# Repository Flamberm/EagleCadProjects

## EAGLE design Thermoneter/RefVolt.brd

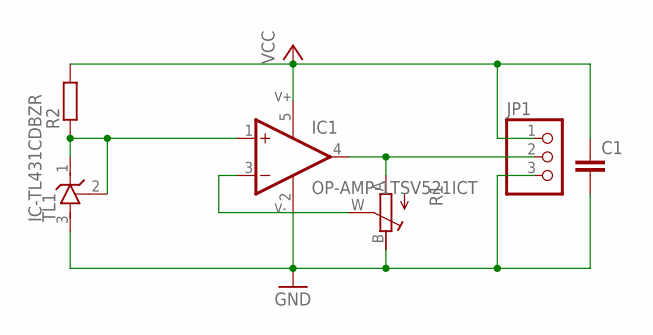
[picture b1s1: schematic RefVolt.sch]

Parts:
C1: CAP_0805; C0805
IC1: OP-AMP-1TSV521ICT; SC70-5L
JP1: PINHD-1X3/90; 1X03/90
R1: R_POTTURN-X; RJ9W
R2: R_0805; R0805
TL1: IC-TL431CDBZR; SOT23

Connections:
GND: C1.2, IC1.2 (V-), JP1.3, R1.B (E), TL1.3 (A)
unnamed: IC1.3 (-IN), R1.W (S)
unnamed: IC1.4 (OUT), JP1.2, R1.A
unnamed: IC1.1 (+IN), R2.1, TL1.1 (C), TL1.2 (R)
VCC: C1.1, IC1.5 (V+), JP1.1, R2.2

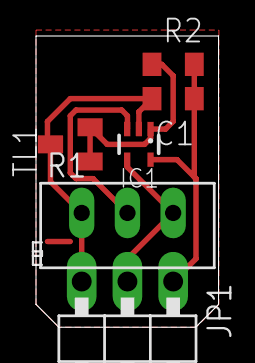
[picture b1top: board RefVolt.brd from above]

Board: 2 copper layers, 10.1 x 16.2 mm, 6 parts (0 on the bottom side), 5 nets.

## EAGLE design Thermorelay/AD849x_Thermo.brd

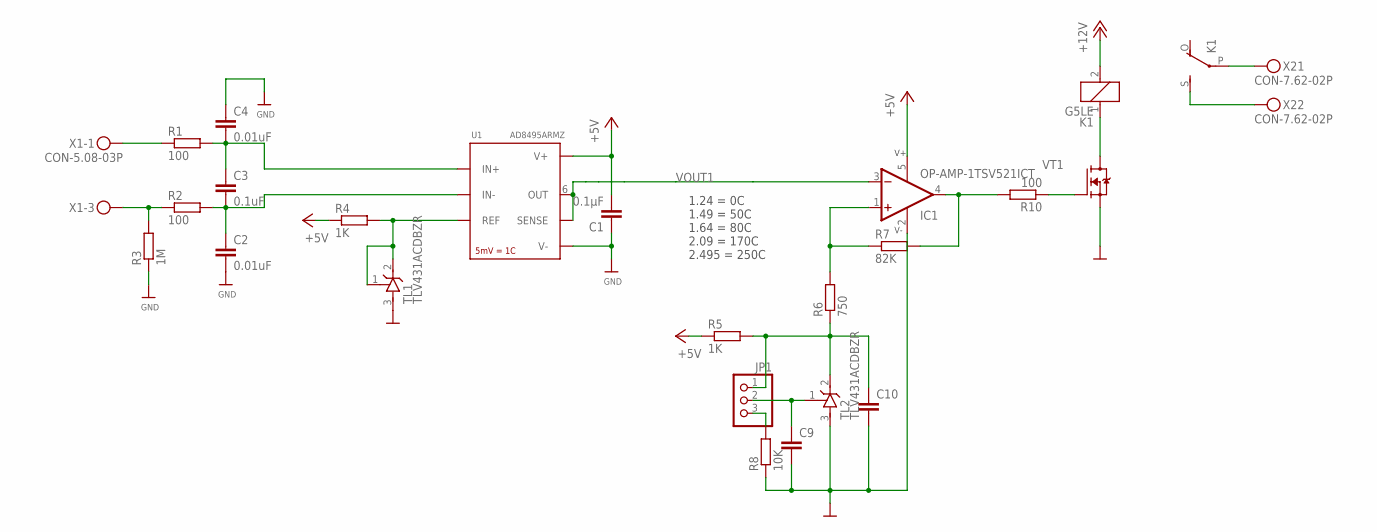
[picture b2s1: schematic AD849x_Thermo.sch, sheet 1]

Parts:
C1: 0.1µF; CAP0805
C2, C4: 0.01uF; CAP0805
C3: 0.1uF; CAP0805
C9, C10: CAP_1206; CAP1206
IC1: OP-AMP-1TSV521ICT; SC70-5L
JP1: PINHD-1X3; 1X03
K1: G5LE
R1, R2, R10: 100; RESC2012X50
R3: 1M; RESC2012X50
R4, R5: 1K; RESC2012X50
R6: 750; RESC2012X50
R7: 82K; RESC2012X50
R8: 10K; RESC2012X50
TL1, TL2: TLV431ACDBZR; SOT95P240X115-3
U1: AD8495ARMZ; MSOP-8
VT1: FET-NSOT-23; SOT95P240X115-3
X1: CON-5.08-03P; MKDSN1,5/3-5,08
X2: CON-7.62-02P; KF25C-7.62-02P-13

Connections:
+5V: C1.2, IC1.5 (V+), R4.1, R5.1, U1.7 (V+); also elsewhere on the board
+12V: K1.2; also elsewhere on the board
GND: C1.1, C2.2, C4.1, C9.2, C10.2, IC1.2 (V-), R3.1, R8.1, TL1.3 (A), TL2.3 (A), U1.3 (V-), VT1.2 (S); also elsewhere on the board
IN+: R1.1, X1.1
IN-: R2.1, R3.2, X1.3
unnamed: R4.2, TL1.1 (R), TL1.2 (C), U1.2 (REF)
unnamed: C3.1, C4.2, R1.2, U1.8 (IN+)
unnamed: C2.1, C3.2, R2.2, U1.1 (IN-)
unnamed: C10.1, JP1.1, R5.2, R6.1, TL2.2 (C)
unnamed: IC1.4 (OUT), R7.2, R10.2
unnamed: IC1.1 (+IN), R6.2, R7.1
unnamed: JP1.3, R8.2
unnamed: C9.1, JP1.2, TL2.1 (R)
unnamed: R10.1, VT1.1 (G)
unnamed: K1.1, VT1.3 (D)
unnamed: K1.P, X2.P$1
unnamed: K1.S, X2.P$2
VOUT1: IC1.3 (-IN), U1.5 (SENSE), U1.6 (OUT)

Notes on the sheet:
1.24 = 0C 1.49 = 50C 1.64 = 80C 2.09 = 170C 2.495 = 250C

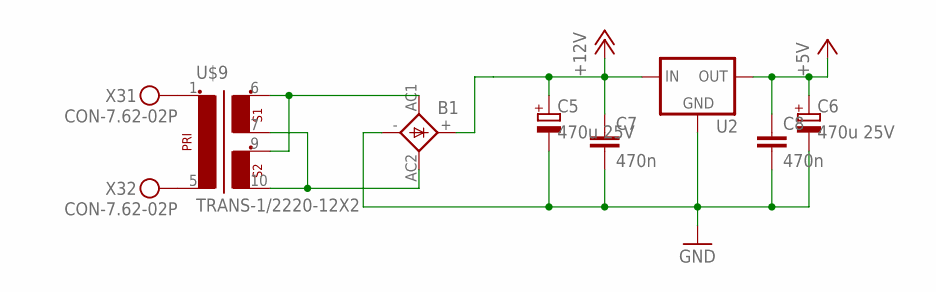
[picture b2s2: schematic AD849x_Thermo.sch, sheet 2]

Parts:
B1: BRIDGEDBS; DBS
C5, C6: 470u 25V; E2,5-7
C7, C8: 470n; CAP1206
U2: V-REGDPAK; DPAK
U$9: TRANS-1/2220-12X2; 32.5-27.5-22
X3: CON-7.62-02P; KF25C-7.62-02P-13

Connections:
+5V: C6.+, C8.1, U2.3 (OUT); also elsewhere on the board
+12V: B1.+, C5.+, C7.1, U2.1 (IN); also elsewhere on the board
GND: B1.-, C5.-, C6.-, C7.2, C8.2, U2.2(PAD) (GND); also elsewhere on the board
unnamed: U$9.5 (P1-2), X3.P$2
unnamed: U$9.1 (P1-1), X3.P$1
unnamed: B1.AC1, U$9.6 (S1-1), U$9.9 (S2-1)
unnamed: B1.AC2, U$9.7 (S1-2), U$9.10 (S2-2)

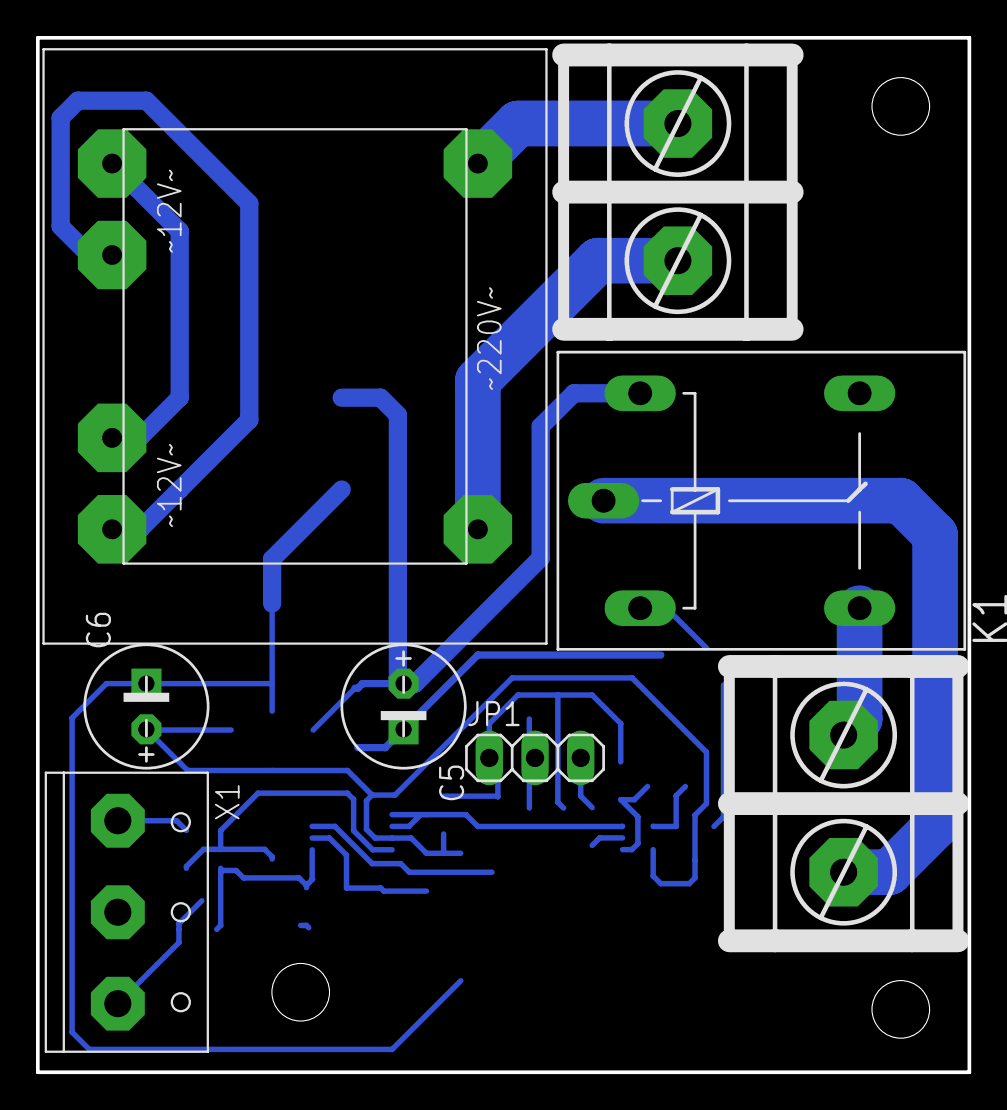
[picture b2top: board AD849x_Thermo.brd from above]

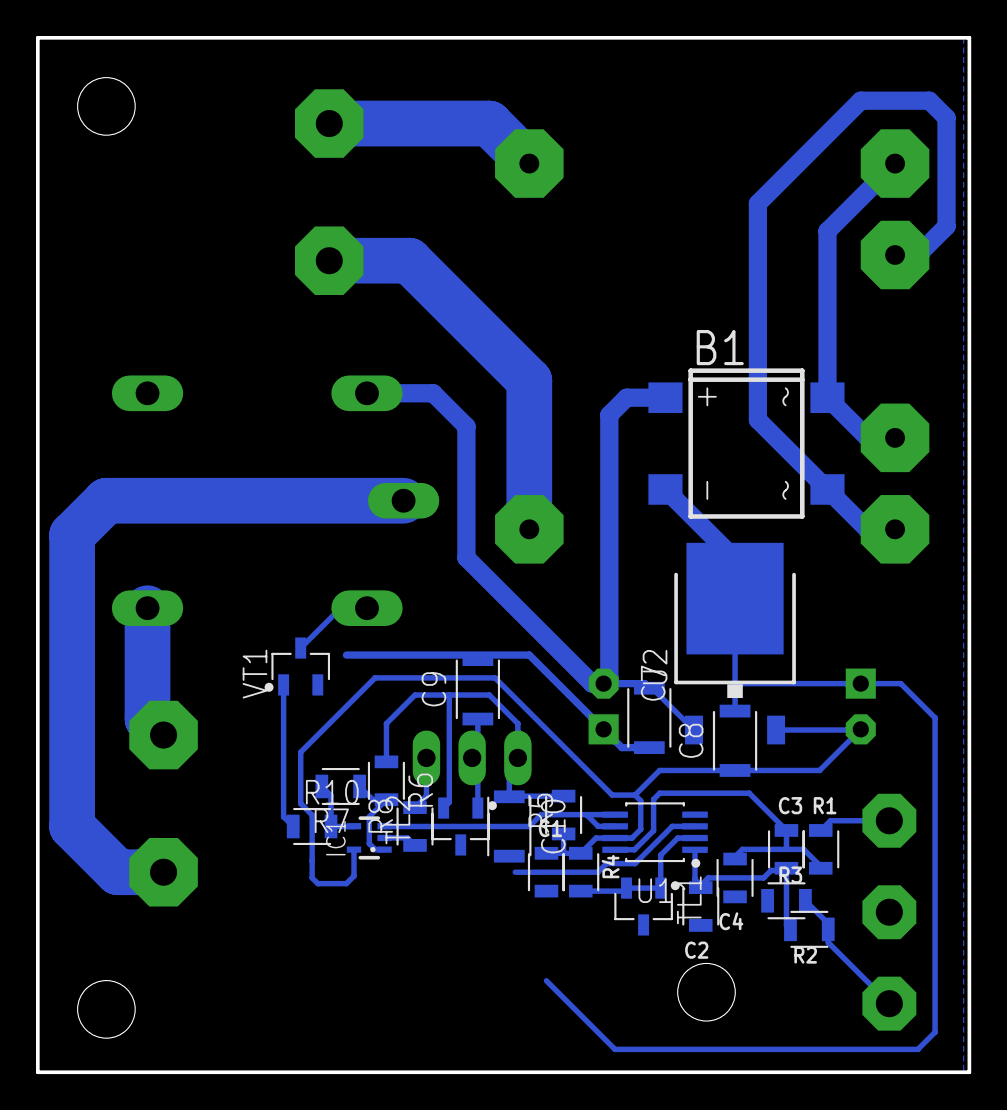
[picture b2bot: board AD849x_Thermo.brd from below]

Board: 2 copper layers, 51.8 x 57.5 mm, 32 parts (24 on the bottom side), 22 nets.

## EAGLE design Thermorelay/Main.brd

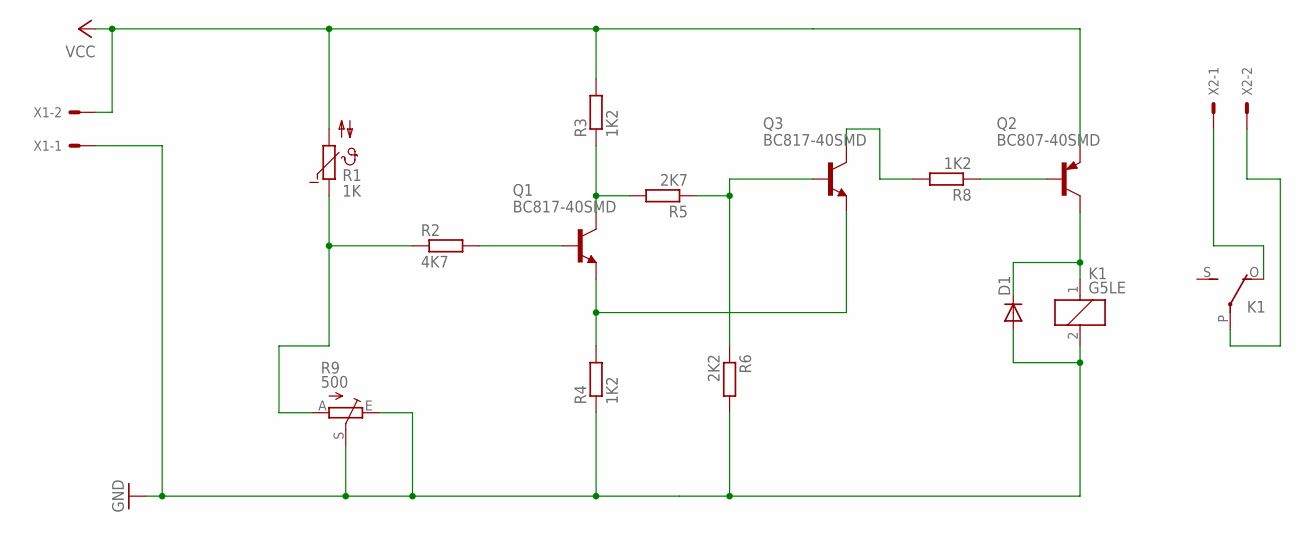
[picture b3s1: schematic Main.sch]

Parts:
D1: DIODE-DO214AC; DO214AC
K1: G5LE
Q1, Q3: BC817-40SMD; SOT23-BEC
Q2: BC807-40SMD; SOT23-BEC
R1: 1K; B57164
R2: 4K7; R1206
R3, R4, R8: 1K2; R1206
R5: 2K7; R1206
R6: 2K2; R1206
R9: 500; CA14V
X1, X2: KK-156-2

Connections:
GND: D1.A, K1.2, R4.1, R6.2, R9.E, R9.S, X1.1
unnamed: D1.C, K1.1, Q2.C
unnamed: Q1.E, Q3.E, R4.2
unnamed: R1.1, R2.1, R9.A
unnamed: Q1.B, R2.2
unnamed: Q1.C, R3.1, R5.2
unnamed: Q3.B, R5.1, R6.1
unnamed: Q3.C, R8.2
unnamed: Q2.B, R8.1
unnamed: K1.O, X2.1
unnamed: K1.P, X2.2
VCC: Q2.E, R1.2, R3.2, X1.2

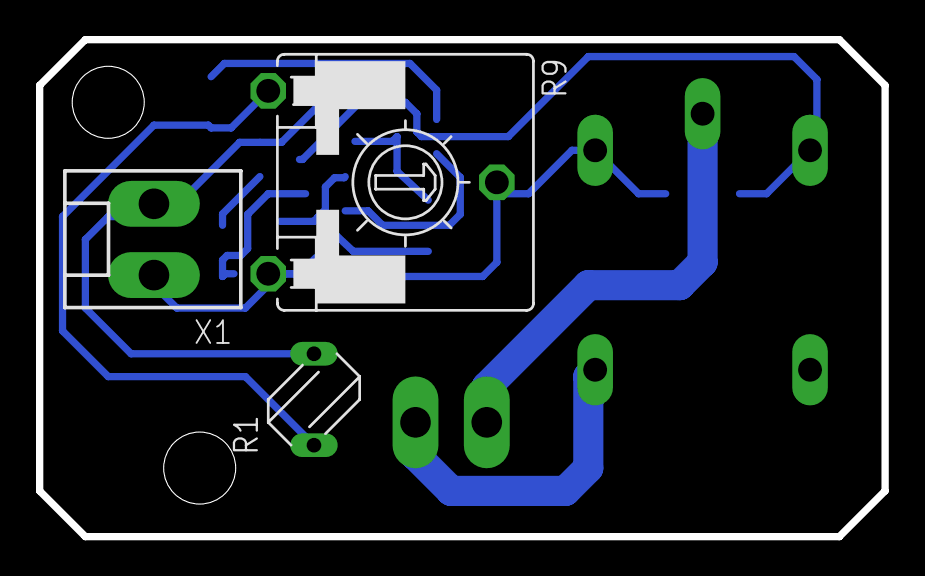
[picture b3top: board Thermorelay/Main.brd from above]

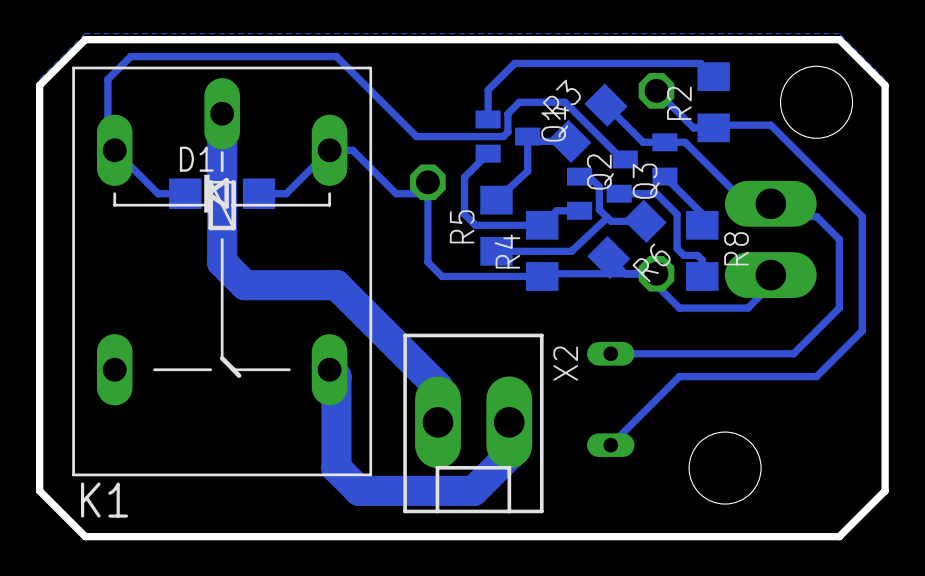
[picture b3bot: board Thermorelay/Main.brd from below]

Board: 2 copper layers, 47.0 x 27.6 mm, 15 parts (12 on the bottom side), 12 nets.

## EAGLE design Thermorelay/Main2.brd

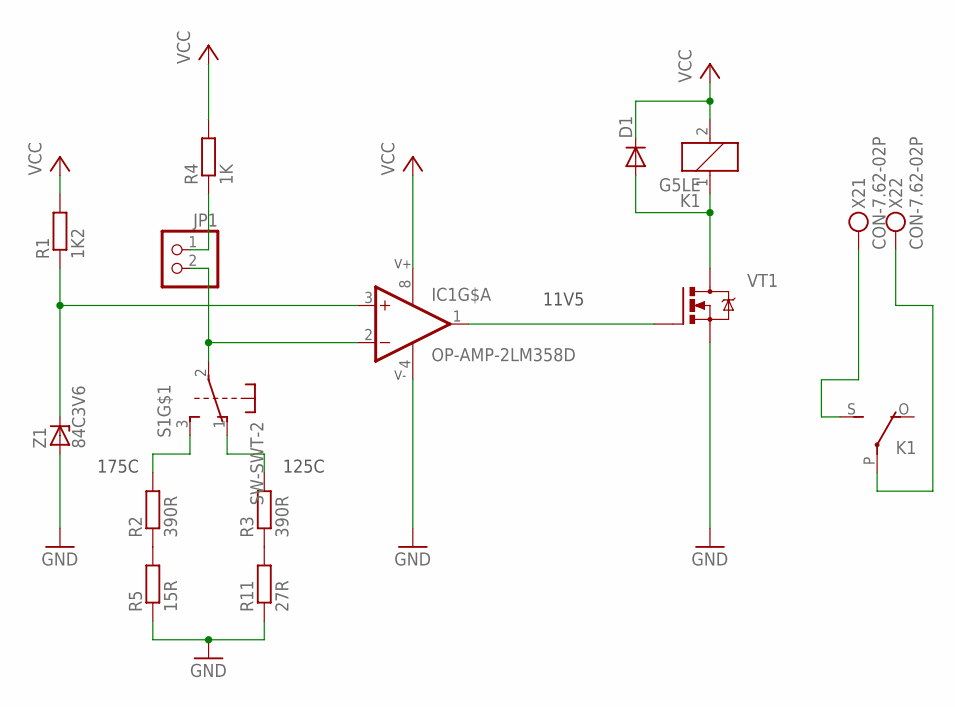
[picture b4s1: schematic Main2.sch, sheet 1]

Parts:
D1: DIODE_ES1J; DO214AC
IC1: OP-AMP-2LM358D; SO8
JP1: PINHD-1X2; 1X02
K1: G5LE
R1: 1K2; R1206
R2, R3: 390R; R0805
R4: 1K; R1206
R5: 15R; R0805
R11: 27R; R0805
S1: SW-SWT-2; SWT-2
VT1: FET-NPF-2X2; POWERFLAT-2X2
X2: CON-7.62-02P; KF25C-7.62-02P-13
Z1: 84C3V6; SOT23

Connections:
GND: IC1.4 (V-), R5.1, R11.1, VT1.S, VT1.S4 (S), Z1.1 (A); also elsewhere on the board
unnamed: IC1.1 (OUT), VT1.G3 (G)
unnamed: IC1.3 (+IN), R1.1, Z1.3 (C)
unnamed: IC1.2 (-IN), JP1.2, S1.2
unnamed: R2.2, S1.3
unnamed: R3.2, S1.1
unnamed: JP1.1, R4.1
unnamed: R2.1, R5.2
unnamed: K1.S, X2.P$1
unnamed: K1.P, X2.P$2
unnamed: R3.1, R11.2
unnamed: D1.A, K1.1, VT1.D, VT1.D1 (D), VT1.D2 (D), VT1.D5 (D), VT1.D6 (D)
VCC: D1.C, IC1.8 (V+), K1.2, R1.2, R4.2; also elsewhere on the board

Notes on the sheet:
125C
175C
11V5

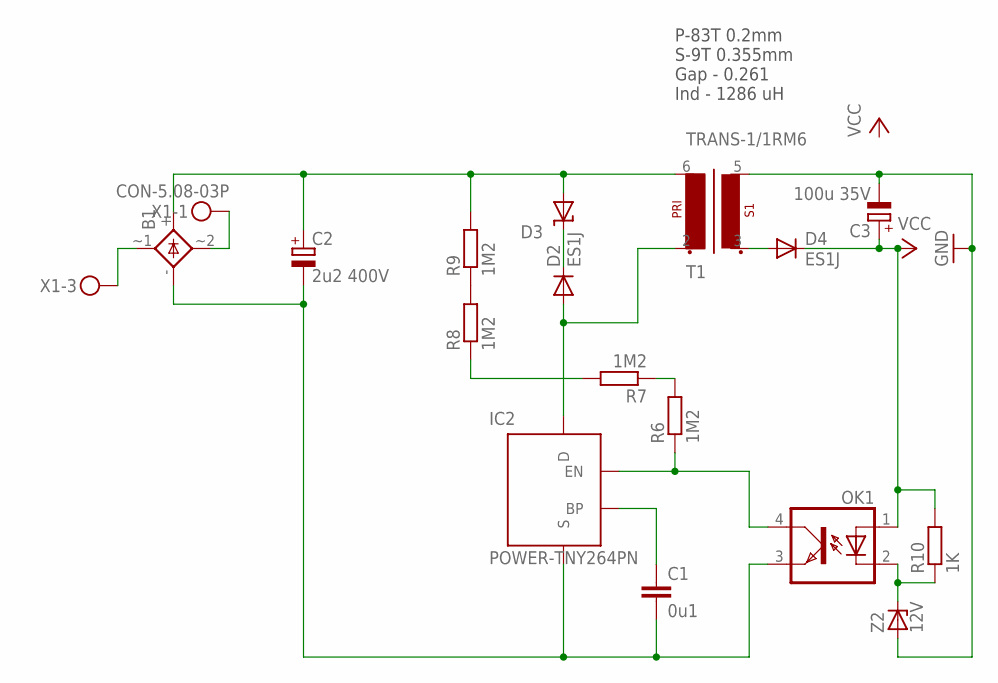
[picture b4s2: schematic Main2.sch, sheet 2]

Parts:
B1: RECTIFIERSOIC-8; SOIC-4
C1: 0u1; C0805
C2: 2u2 400V; E2,5-7
C3: 100u 35V; E3,5-8
D2, D4: ES1J; DO214AC
D3: SUPRESSORDO-204AC; DO15-12
IC2: POWER-TNY264PN; DIP-8B
OK1: OPTOTRANSPC817; DIL04
R6, R7, R8, R9: 1M2; R0805
R10: 1K; R1206
T1: TRANS-1/1RM6; RM6
X1: CON-5.08-03P; MKDSN1,5/3-5,08
Z2: 12V; MINIMELF

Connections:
GND: C3.-, T1.5 (S1-2), Z2.A; also elsewhere on the board
unnamed: C1.1, IC2.1 (BP)
unnamed: IC2.4 (EN), OK1.4 (COL), R6.1
unnamed: B1.-, C1.2, C2.-, IC2.2 (S), IC2.3 (S), IC2.7 (S), IC2.8 (S), OK1.3 (EMIT)
unnamed: R6.2, R7.1
unnamed: R7.2, R8.1
unnamed: R8.2, R9.1
unnamed: B1.+, C2.+, D3.A, R9.2, T1.6 (P1-2)
unnamed: D2.A, IC2.5 (D), T1.2 (P1-1)
unnamed: D2.C, D3.C
unnamed: B1.~2 (AC2), X1.1
unnamed: D4.A, T1.3 (S1-1)
unnamed: OK1.2 (C), R10.1, Z2.C
unnamed: B1.~1 (AC1), X1.3
VCC: C3.+, D4.C, OK1.1 (A), R10.2; also elsewhere on the board

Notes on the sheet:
P-83T 0.2mm S-9T 0.355mm Gap - 0.261 Ind - 1286 uH

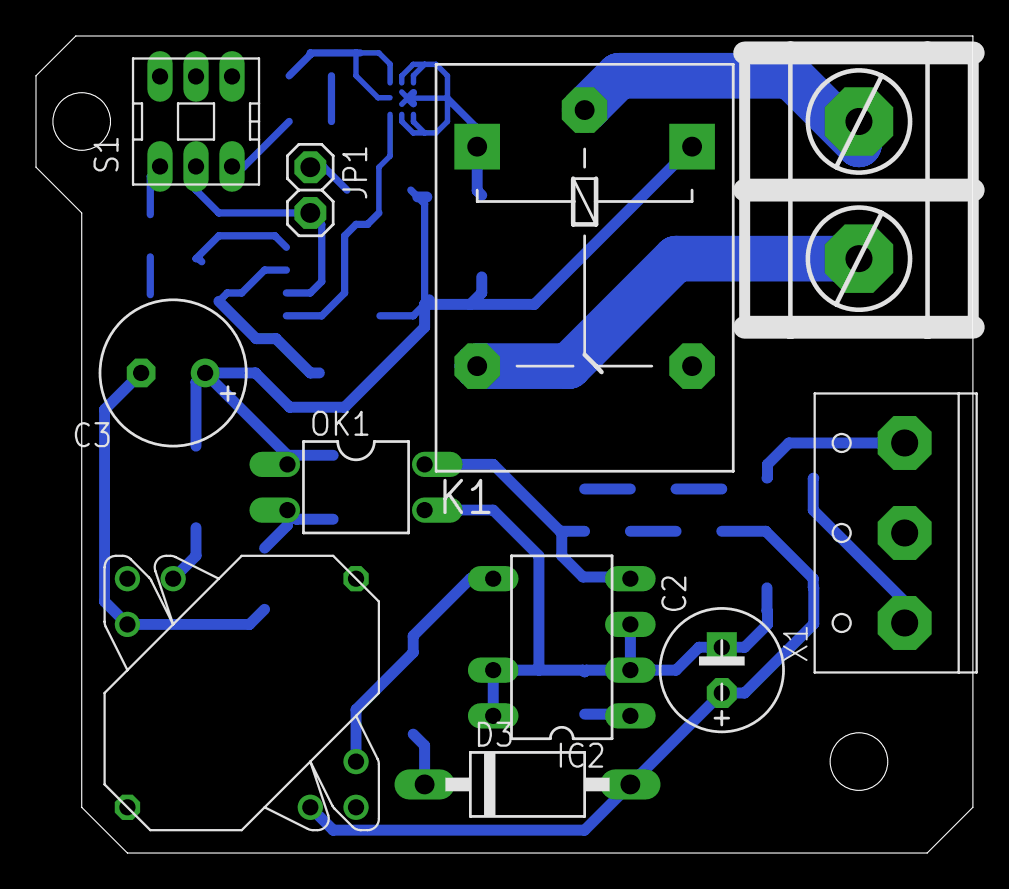
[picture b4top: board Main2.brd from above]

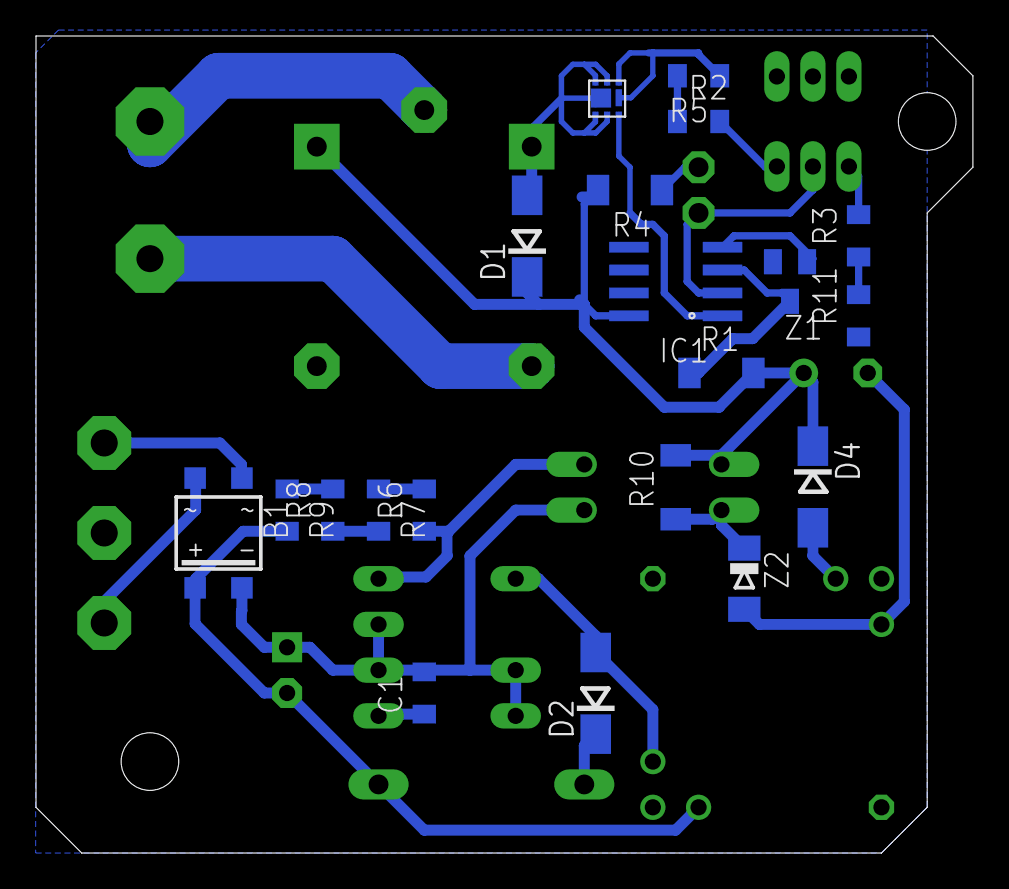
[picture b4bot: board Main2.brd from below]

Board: 2 copper layers, 52.0 x 45.4 mm, 31 parts (20 on the bottom side), 26 nets.

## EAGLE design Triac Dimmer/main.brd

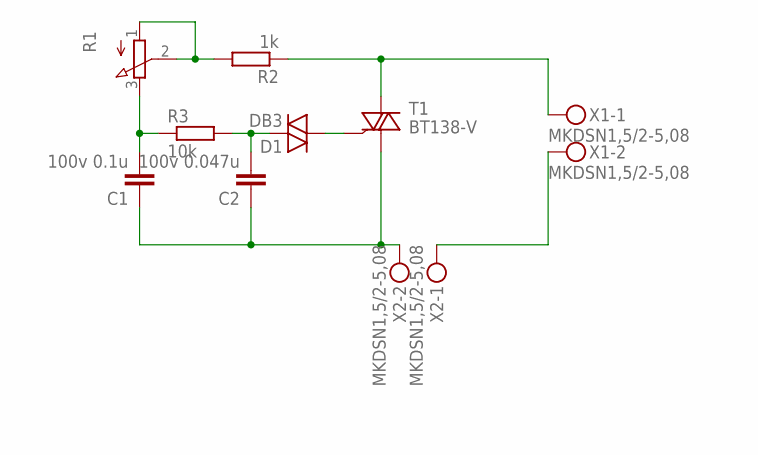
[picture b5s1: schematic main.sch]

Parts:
C1: 100v 0.1u; C102-054X133
C2: 100v 0.047u; C075-042X103
D1: DB3; GT32
R1: 3RP/1610N
R2: 1k; 0309/10
R3: 10k; 0309/10
T1: BT138-V; TO220BV
X1, X2: MKDSN1,5/2-5,08

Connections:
unnamed: X1.2, X2.1
unnamed: C1.1, C2.1, T1.T1 (A1), X2.2
unnamed: D1.1, T1.G
unnamed: C1.2, R1.3 (E), R3.1
unnamed: R2.1, T1.T2 (A2), X1.1
unnamed: R1.1 (A), R1.2 (S), R2.2
unnamed: C2.2, D1.2, R3.2

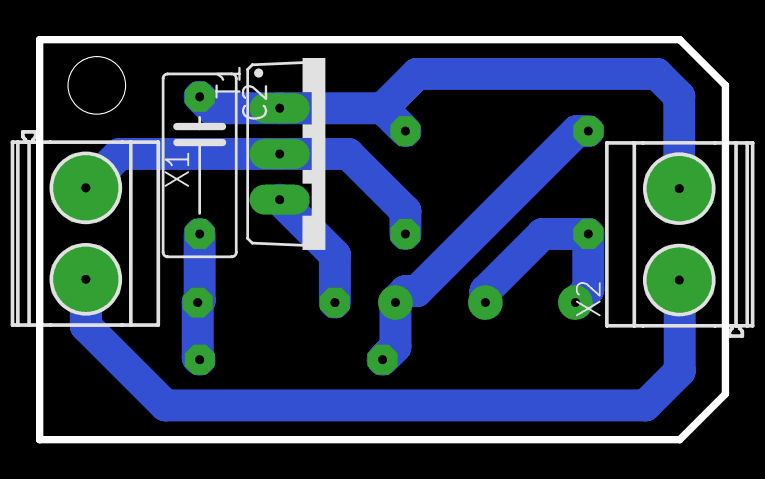
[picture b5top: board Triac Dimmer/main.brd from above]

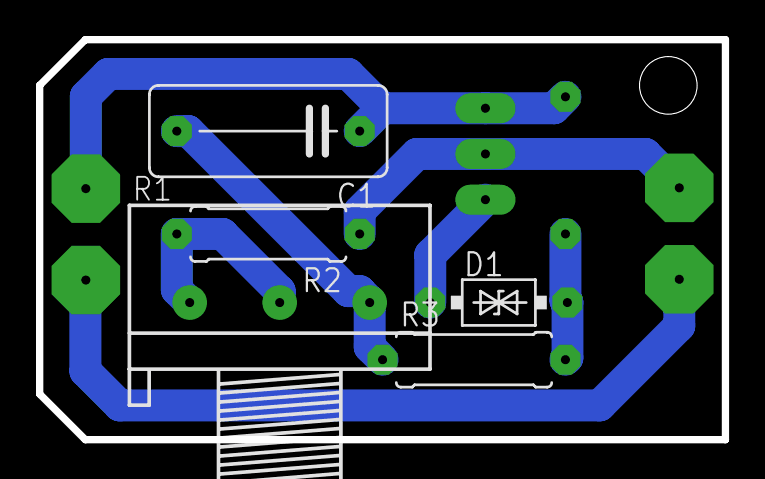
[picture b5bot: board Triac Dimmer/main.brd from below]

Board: 2 copper layers, 38.1 x 22.2 mm, 9 parts (5 on the bottom side), 7 nets.

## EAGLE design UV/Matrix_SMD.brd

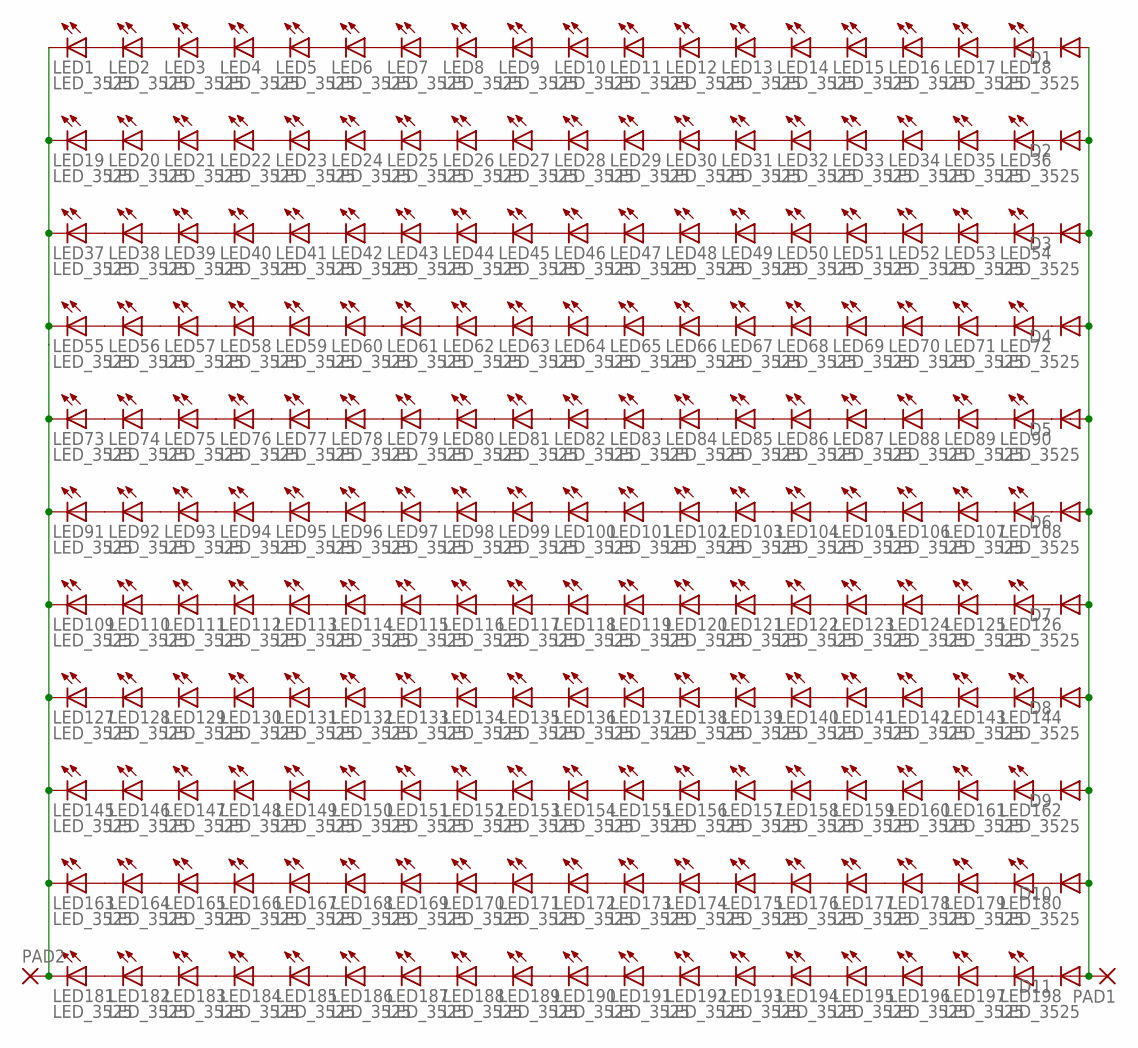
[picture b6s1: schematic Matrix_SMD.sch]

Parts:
D1, D2, D3, D4, D5, D6, D7, D8, D9, D10, D11: DIODE-SOD123; SOD123
LED1, LED2, LED3, LED4, LED5, LED6, LED7, LED8, LED9, LED10, LED11, LED12, LED13, LED14, LED15, LED16, LED17, LED18, LED19, LED20, LED21, LED22, LED23, LED24, LED25, LED26, LED27, LED28, LED29, LED30, LED31, LED32, LED33, LED34, LED35, LED36, LED37, LED38, LED39, LED40, LED41, LED42, LED43, LED44, LED45, LED46, LED47, LED48, LED49, LED50, LED51, LED52, LED53, LED54, LED55, LED56, LED57, LED58, LED59, LED60, LED61, LED62, LED63, LED64, LED65, LED66, LED67, LED68, LED69, LED70, LED71, LED72, LED73, LED74, LED75, LED76, LED77, LED78, LED79, LED80, LED81, LED82, LED83, LED84, LED85, LED86, LED87, LED88, LED89, LED90, LED91, LED92, LED93, LED94, LED95, LED96, LED97, LED98, LED99, LED100, LED101, LED102, LED103, LED104, LED105, LED106, LED107, LED108, LED109, LED110, LED111, LED112, LED113, LED114, LED115, LED116, LED117, LED118, LED119, LED120, LED121, LED122, LED123, LED124, LED125, LED126, LED127, LED128, LED129, LED130, LED131, LED132, LED133, LED134, LED135, LED136, LED137, LED138, LED139, LED140, LED141, LED142, LED143, LED144, LED145, LED146, LED147, LED148, LED149, LED150, LED151, LED152, LED153, LED154, LED155, LED156, LED157, LED158, LED159, LED160, LED161, LED162, LED163, LED164, LED165, LED166, LED167, LED168, LED169, LED170, LED171, LED172, LED173, LED174, LED175, LED176, LED177, LED178, LED179, LED180, LED181, LED182, LED183, LED184, LED185, LED186, LED187, LED188, LED189, LED190, LED191, LED192, LED193, LED194, LED195, LED196, LED197, LED198: LED_3525; LED3528
PAD1, PAD2: 3,81/1,4

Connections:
unnamed: LED1.A, LED2.C
unnamed: LED2.A, LED3.C
unnamed: LED3.A, LED4.C
unnamed: LED4.A, LED5.C
unnamed: LED5.A, LED6.C
unnamed: LED6.A, LED7.C
unnamed: LED7.A, LED8.C
unnamed: LED8.A, LED9.C
unnamed: LED9.A, LED10.C
unnamed: LED10.A, LED11.C
unnamed: LED11.A, LED12.C
unnamed: LED12.A, LED13.C
unnamed: LED13.A, LED14.C
unnamed: LED14.A, LED15.C
unnamed: LED15.A, LED16.C
unnamed: LED16.A, LED17.C
unnamed: LED17.A, LED18.C
unnamed: D1.C, LED18.A
unnamed: LED19.A, LED20.C
unnamed: LED20.A, LED21.C
unnamed: LED21.A, LED22.C
unnamed: LED22.A, LED23.C
unnamed: LED23.A, LED24.C
unnamed: LED24.A, LED25.C
unnamed: LED25.A, LED26.C
unnamed: LED26.A, LED27.C
unnamed: LED27.A, LED28.C
unnamed: LED28.A, LED29.C
unnamed: LED29.A, LED30.C
unnamed: LED30.A, LED31.C
unnamed: LED31.A, LED32.C
unnamed: LED32.A, LED33.C
unnamed: LED33.A, LED34.C
unnamed: LED34.A, LED35.C
unnamed: LED35.A, LED36.C
unnamed: D2.C, LED36.A
unnamed: LED37.A, LED38.C
unnamed: LED38.A, LED39.C
unnamed: LED39.A, LED40.C
unnamed: LED40.A, LED41.C
unnamed: LED41.A, LED42.C
unnamed: LED42.A, LED43.C
unnamed: LED43.A, LED44.C
unnamed: LED44.A, LED45.C
unnamed: LED45.A, LED46.C
unnamed: LED46.A, LED47.C
unnamed: LED47.A, LED48.C
unnamed: LED48.A, LED49.C
unnamed: LED49.A, LED50.C
unnamed: LED50.A, LED51.C
unnamed: LED51.A, LED52.C
unnamed: LED52.A, LED53.C
unnamed: LED53.A, LED54.C
unnamed: D3.C, LED54.A
unnamed: LED55.A, LED56.C
unnamed: LED56.A, LED57.C
unnamed: LED57.A, LED58.C
unnamed: LED58.A, LED59.C
unnamed: LED59.A, LED60.C
unnamed: LED60.A, LED61.C
unnamed: LED61.A, LED62.C
unnamed: LED62.A, LED63.C
unnamed: LED63.A, LED64.C
unnamed: LED64.A, LED65.C
unnamed: LED65.A, LED66.C
unnamed: LED66.A, LED67.C
unnamed: LED67.A, LED68.C
unnamed: LED68.A, LED69.C
unnamed: LED69.A, LED70.C
unnamed: LED70.A, LED71.C
unnamed: LED71.A, LED72.C
unnamed: D4.C, LED72.A
unnamed: LED73.A, LED74.C
unnamed: LED74.A, LED75.C
unnamed: LED75.A, LED76.C
unnamed: LED76.A, LED77.C
unnamed: LED77.A, LED78.C
unnamed: LED78.A, LED79.C
unnamed: LED79.A, LED80.C
unnamed: LED80.A, LED81.C
unnamed: LED81.A, LED82.C
unnamed: LED82.A, LED83.C
unnamed: LED83.A, LED84.C
unnamed: LED84.A, LED85.C
unnamed: LED85.A, LED86.C
unnamed: LED86.A, LED87.C
unnamed: LED87.A, LED88.C
unnamed: LED88.A, LED89.C
unnamed: LED89.A, LED90.C
unnamed: D5.C, LED90.A
unnamed: LED91.A, LED92.C
unnamed: LED92.A, LED93.C
unnamed: LED93.A, LED94.C
unnamed: LED94.A, LED95.C
unnamed: LED95.A, LED96.C
unnamed: LED96.A, LED97.C
unnamed: LED97.A, LED98.C
unnamed: LED98.A, LED99.C
unnamed: LED99.A, LED100.C
unnamed: LED100.A, LED101.C
unnamed: LED101.A, LED102.C
unnamed: LED102.A, LED103.C
unnamed: LED103.A, LED104.C
unnamed: LED104.A, LED105.C
unnamed: LED105.A, LED106.C
unnamed: LED106.A, LED107.C
unnamed: LED107.A, LED108.C
unnamed: D6.C, LED108.A
unnamed: LED109.A, LED110.C
unnamed: LED110.A, LED111.C
unnamed: LED111.A, LED112.C
unnamed: LED112.A, LED113.C
unnamed: LED113.A, LED114.C
unnamed: LED114.A, LED115.C
unnamed: LED115.A, LED116.C
unnamed: LED116.A, LED117.C
unnamed: LED117.A, LED118.C
unnamed: LED118.A, LED119.C
unnamed: LED119.A, LED120.C
unnamed: LED120.A, LED121.C
unnamed: LED121.A, LED122.C
unnamed: LED122.A, LED123.C
unnamed: LED123.A, LED124.C
unnamed: LED124.A, LED125.C
unnamed: LED125.A, LED126.C
unnamed: D7.C, LED126.A
unnamed: LED127.A, LED128.C
unnamed: LED128.A, LED129.C
unnamed: LED129.A, LED130.C
unnamed: LED130.A, LED131.C
unnamed: LED131.A, LED132.C
unnamed: LED132.A, LED133.C
unnamed: LED133.A, LED134.C
unnamed: LED134.A, LED135.C
unnamed: LED135.A, LED136.C
unnamed: LED136.A, LED137.C
unnamed: LED137.A, LED138.C
unnamed: LED138.A, LED139.C
unnamed: LED139.A, LED140.C
unnamed: LED140.A, LED141.C
unnamed: LED141.A, LED142.C
unnamed: LED142.A, LED143.C
unnamed: LED143.A, LED144.C
unnamed: D8.C, LED144.A
unnamed: LED145.A, LED146.C
unnamed: LED146.A, LED147.C
unnamed: LED147.A, LED148.C
unnamed: LED148.A, LED149.C
unnamed: LED149.A, LED150.C
unnamed: LED150.A, LED151.C
unnamed: LED151.A, LED152.C
unnamed: LED152.A, LED153.C
unnamed: LED153.A, LED154.C
unnamed: LED154.A, LED155.C
unnamed: LED155.A, LED156.C
unnamed: LED156.A, LED157.C
unnamed: LED157.A, LED158.C
unnamed: LED158.A, LED159.C
unnamed: LED159.A, LED160.C
unnamed: LED160.A, LED161.C
unnamed: LED161.A, LED162.C
unnamed: D9.C, LED162.A
unnamed: LED163.A, LED164.C
unnamed: LED164.A, LED165.C
unnamed: LED165.A, LED166.C
unnamed: LED166.A, LED167.C
unnamed: LED167.A, LED168.C
unnamed: LED168.A, LED169.C
unnamed: LED169.A, LED170.C
unnamed: LED170.A, LED171.C
unnamed: LED171.A, LED172.C
unnamed: LED172.A, LED173.C
unnamed: LED173.A, LED174.C
unnamed: LED174.A, LED175.C
unnamed: LED175.A, LED176.C
unnamed: LED176.A, LED177.C
unnamed: LED177.A, LED178.C
unnamed: LED178.A, LED179.C
unnamed: LED179.A, LED180.C
unnamed: D10.C, LED180.A
unnamed: LED181.A, LED182.C
unnamed: LED182.A, LED183.C
unnamed: LED183.A, LED184.C
unnamed: LED184.A, LED185.C
unnamed: LED185.A, LED186.C
unnamed: LED186.A, LED187.C
unnamed: LED187.A, LED188.C
unnamed: LED188.A, LED189.C
unnamed: LED189.A, LED190.C
unnamed: LED190.A, LED191.C
unnamed: LED191.A, LED192.C
unnamed: LED192.A, LED193.C
unnamed: LED193.A, LED194.C
unnamed: LED194.A, LED195.C
unnamed: LED195.A, LED196.C
unnamed: LED196.A, LED197.C
unnamed: LED197.A, LED198.C
unnamed: D11.C, LED198.A
unnamed: LED1.C, LED19.C, LED37.C, LED55.C, LED73.C, LED91.C, LED109.C, LED127.C, LED145.C, LED163.C, LED181.C, PAD2.1
unnamed: D1.A, D2.A, D3.A, D4.A, D5.A, D6.A, D7.A, D8.A, D9.A, D10.A, D11.A, PAD1.1

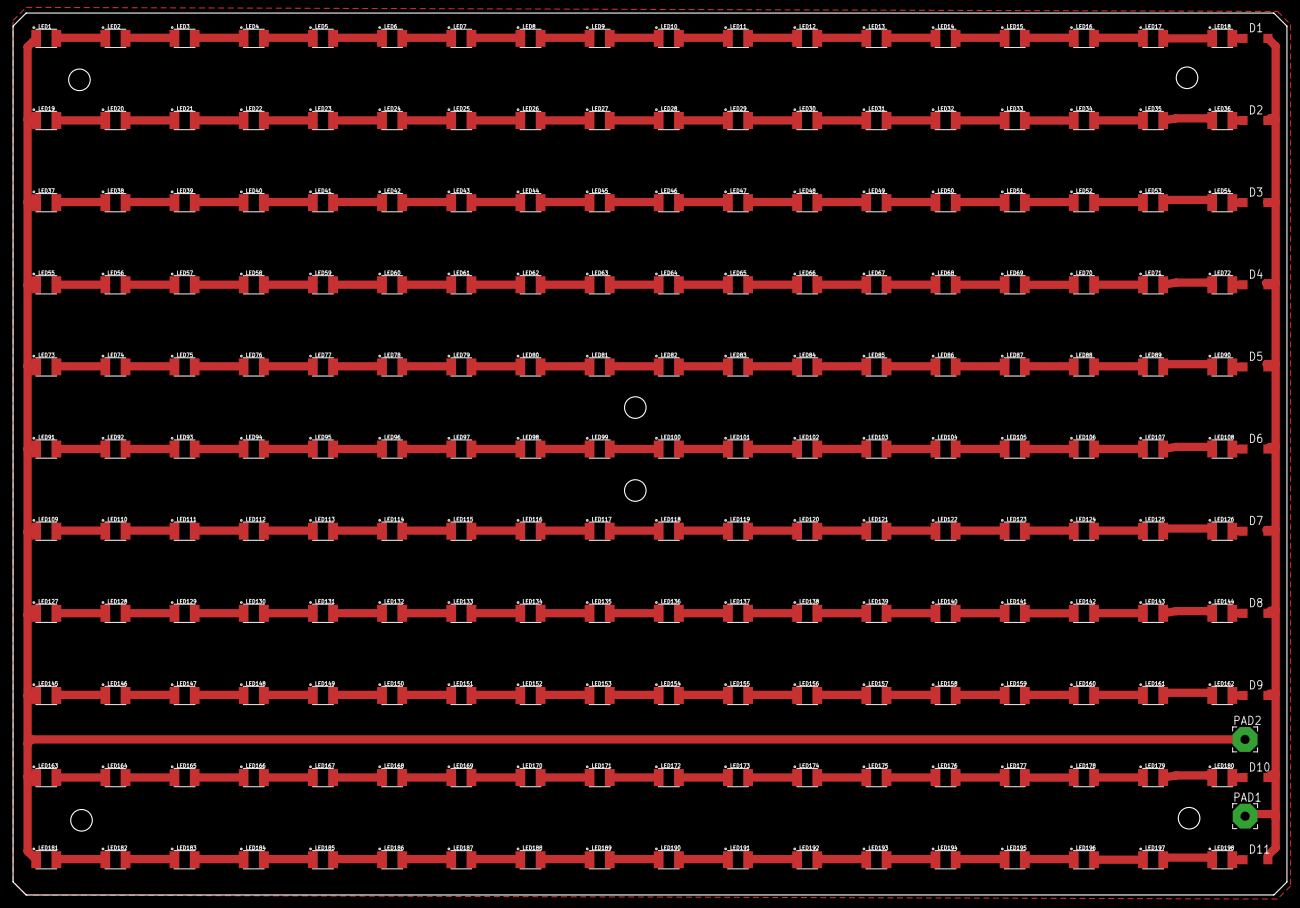
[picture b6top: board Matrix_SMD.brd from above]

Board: 2 copper layers, 195.0 x 135.0 mm, 211 parts (0 on the bottom side), 200 nets.

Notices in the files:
parts and their libraries:
microbuilder: This work is placed in the public domain, and may be freely used for commercial and non-commercial work with the following conditions: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
